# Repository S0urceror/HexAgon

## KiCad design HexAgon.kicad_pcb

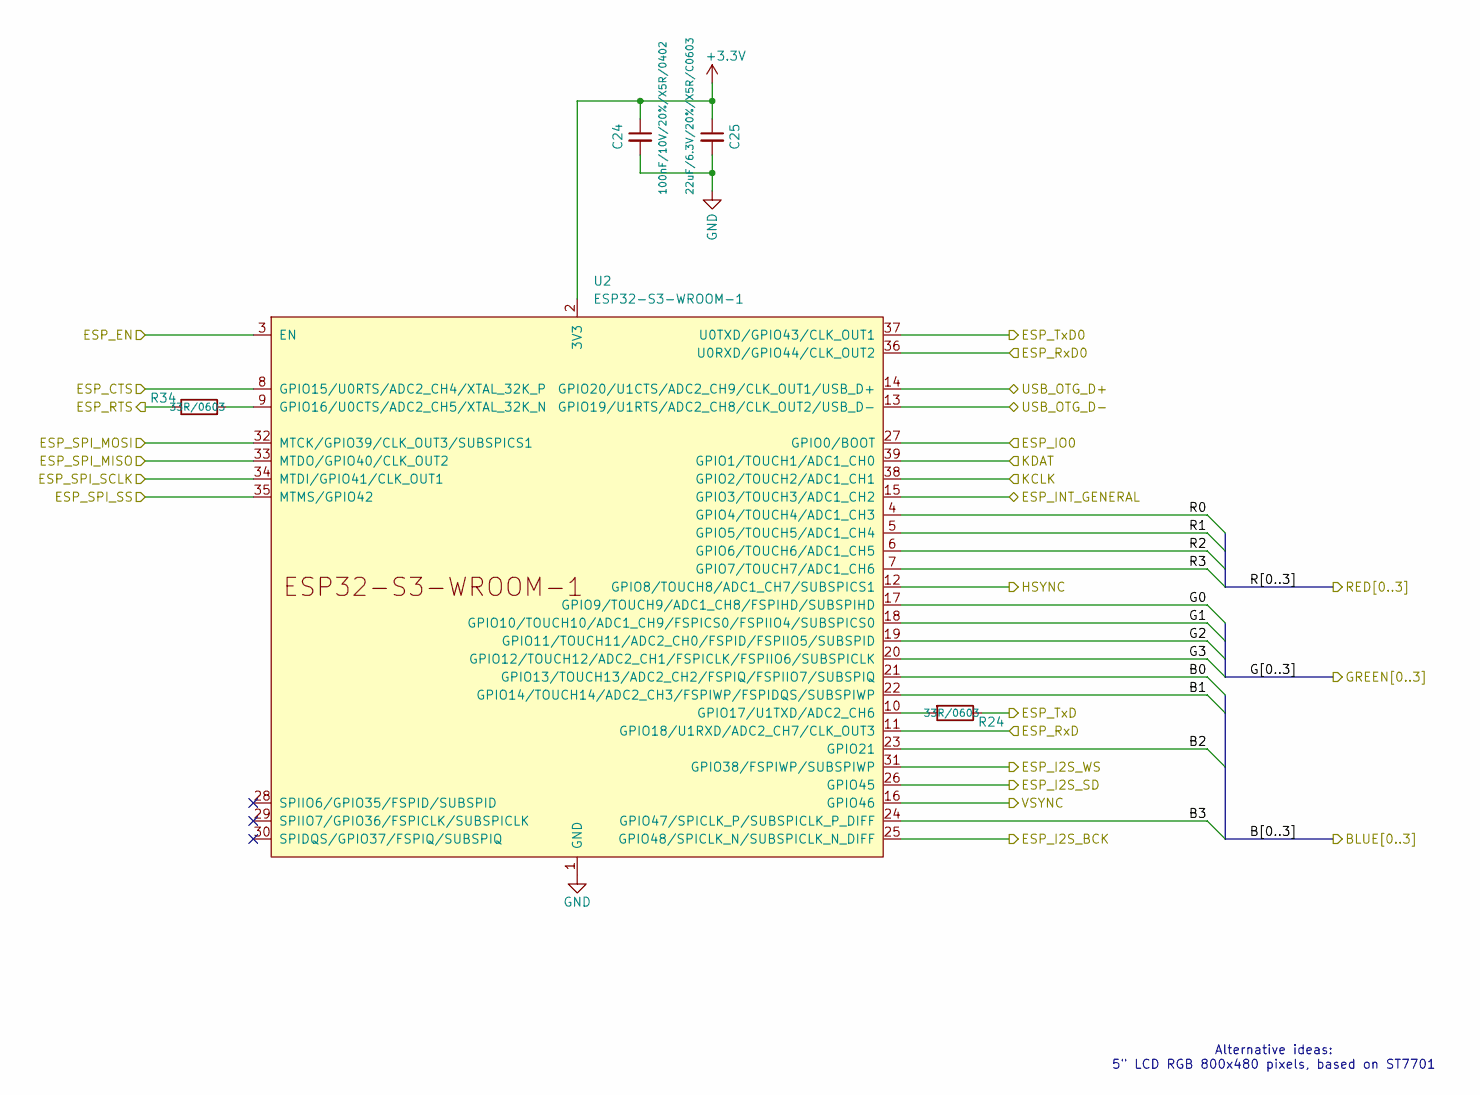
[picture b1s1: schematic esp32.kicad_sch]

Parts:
C24: 100nF/10V/20%/X5R/0402; C_0402_5MIL_DWS
C25: 22uF/6.3V/20%/X5R/C0603; C_0603_5MIL_DWS
R24, R34: 33R/0603; R_0603_5MIL_DWS
U2: ESP32-S3-WROOM-1

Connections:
+3.3V: C24.1, C25.1, U2.2 (3V3); also elsewhere on the board
/Audio/ESP_I2S_BCK: U2.25 (GPIO48/SPICLK_N/SUBSPICLK_N_DIFF); also elsewhere on the board
/Audio/ESP_I2S_SD: U2.26 (GPIO45); also elsewhere on the board
/Audio/ESP_I2S_WS: U2.31 (GPIO38/FSPIWP/SUBSPIWP); also elsewhere on the board
/ESP32 ports/BOOT_MODE: U2.27 (GPIO0/BOOT); also elsewhere on the board
/ESP32 ports/HOST_RXD: U2.37 (U0TXD/GPIO43/CLK_OUT1); also elsewhere on the board
/ESP32 ports/HOST_TXD: U2.36 (U0RXD/GPIO44/CLK_OUT2); also elsewhere on the board
/ESP32 ports/KCLK: U2.38 (GPIO2/TOUCH2/ADC1_CH1); also elsewhere on the board
/ESP32 ports/KDAT: U2.39 (GPIO1/TOUCH1/ADC1_CH0); also elsewhere on the board
/ESP32 ports/USB_OTG_D+: U2.14 (GPIO20/U1CTS/ADC2_CH9/CLK_OUT1/USB_D+); also elsewhere on the board
/ESP32 ports/USB_OTG_D-: U2.13 (GPIO19/U1RTS/ADC2_CH8/CLK_OUT2/USB_D-); also elsewhere on the board
/ESP32/B0: U2.21 (GPIO13/TOUCH13/ADC2_CH2/FSPIQ/FSPIIO7/S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); also elsewhere on the board
/ESP32/B1: U2.22 (GPIO14/TOUCH14/ADC2_CH3/FSPIWP/FSPIDQS/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); also elsewhere on the board
/ESP32/B2: U2.23 (GPIO21); also elsewhere on the board
/ESP32/B3: U2.24 (GPIO47/SPICLK_P/SUBSPICLK_P_DIFF); also elsewhere on the board
/ESP32/ESP_CTS: U2.8 (GPIO15/U0RTS/ADC2_CH4/XTAL_32K_P); also elsewhere on the board
/ESP32/ESP_INT_GENERAL: U2.15 (GPIO3/TOUCH3/ADC1_CH2); also elsewhere on the board
/ESP32/ESP_RTS: R34.1; also elsewhere on the board
/ESP32/ESP_RxD: U2.11 (GPIO18/U1RXD/ADC2_CH7/CLK_OUT3); also elsewhere on the board
/ESP32/ESP_SPI_MISO: U2.33 (MTDO/GPIO40/CLK_OUT2); also elsewhere on the board
/ESP32/ESP_SPI_MOSI: U2.32 (MTCK/GPIO39/CLK_OUT3/SUBSPICS1); also elsewhere on the board
/ESP32/ESP_SPI_SCLK: U2.34 (MTDI/GPIO41/CLK_OUT1); also elsewhere on the board
/ESP32/ESP_SPI_SS: U2.35 (MTMS/GPIO42); also elsewhere on the board
/ESP32/ESP_TxD: R24.1; also elsewhere on the board
/ESP32/G0: U2.17 (GPIO9/TOUCH9/ADC1_CH8/FSPIHD/SUBSPIHD); also elsewhere on the board
/ESP32/G1: U2.18 (GPIO10/TOUCH10/ADC1_CH9/FSPICS0/FSPIIO4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); also elsewhere on the board
/ESP32/G2: U2.19 (GPIO11/TOUCH11/ADC2_CH0/FSPID/FSPIIO5/S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); also elsewhere on the board
/ESP32/G3: U2.20 (GPIO12/TOUCH12/ADC2_CH1/FSPICLK/FSPIIO6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); also elsewhere on the board
/ESP32/HSYNC: U2.12 (GPIO8/TOUCH8/ADC1_CH7/SUBSPICS1); also elsewhere on the board
/ESP32/R0: U2.4 (GPIO4/TOUCH4/ADC1_CH3); also elsewhere on the board
/ESP32/R1: U2.5 (GPIO5/TOUCH5/ADC1_CH4); also elsewhere on the board
/ESP32/R2: U2.6 (GPIO6/TOUCH6/ADC1_CH5); also elsewhere on the board
/ESP32/R3: U2.7 (GPIO7/TOUCH7/ADC1_CH6); also elsewhere on the board
/ESP32/VSYNC: U2.16 (GPIO46); also elsewhere on the board
/EZ80/~RESET: U2.3 (EN); also elsewhere on the board
GND: C24.2, C25.2, U2.1 (GND), U2.40 (GND), U2.41 (GND); also elsewhere on the board
unnamed: R34.2, U2.9 (GPIO16/U0CTS/ADC2_CH5/XTAL_32K_N)
unnamed: R24.2, U2.10 (GPIO17/U1TXD/ADC2_CH6)

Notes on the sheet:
Alternative ideas: 5" LCD RGB 800x480 pixels, based on ST7701

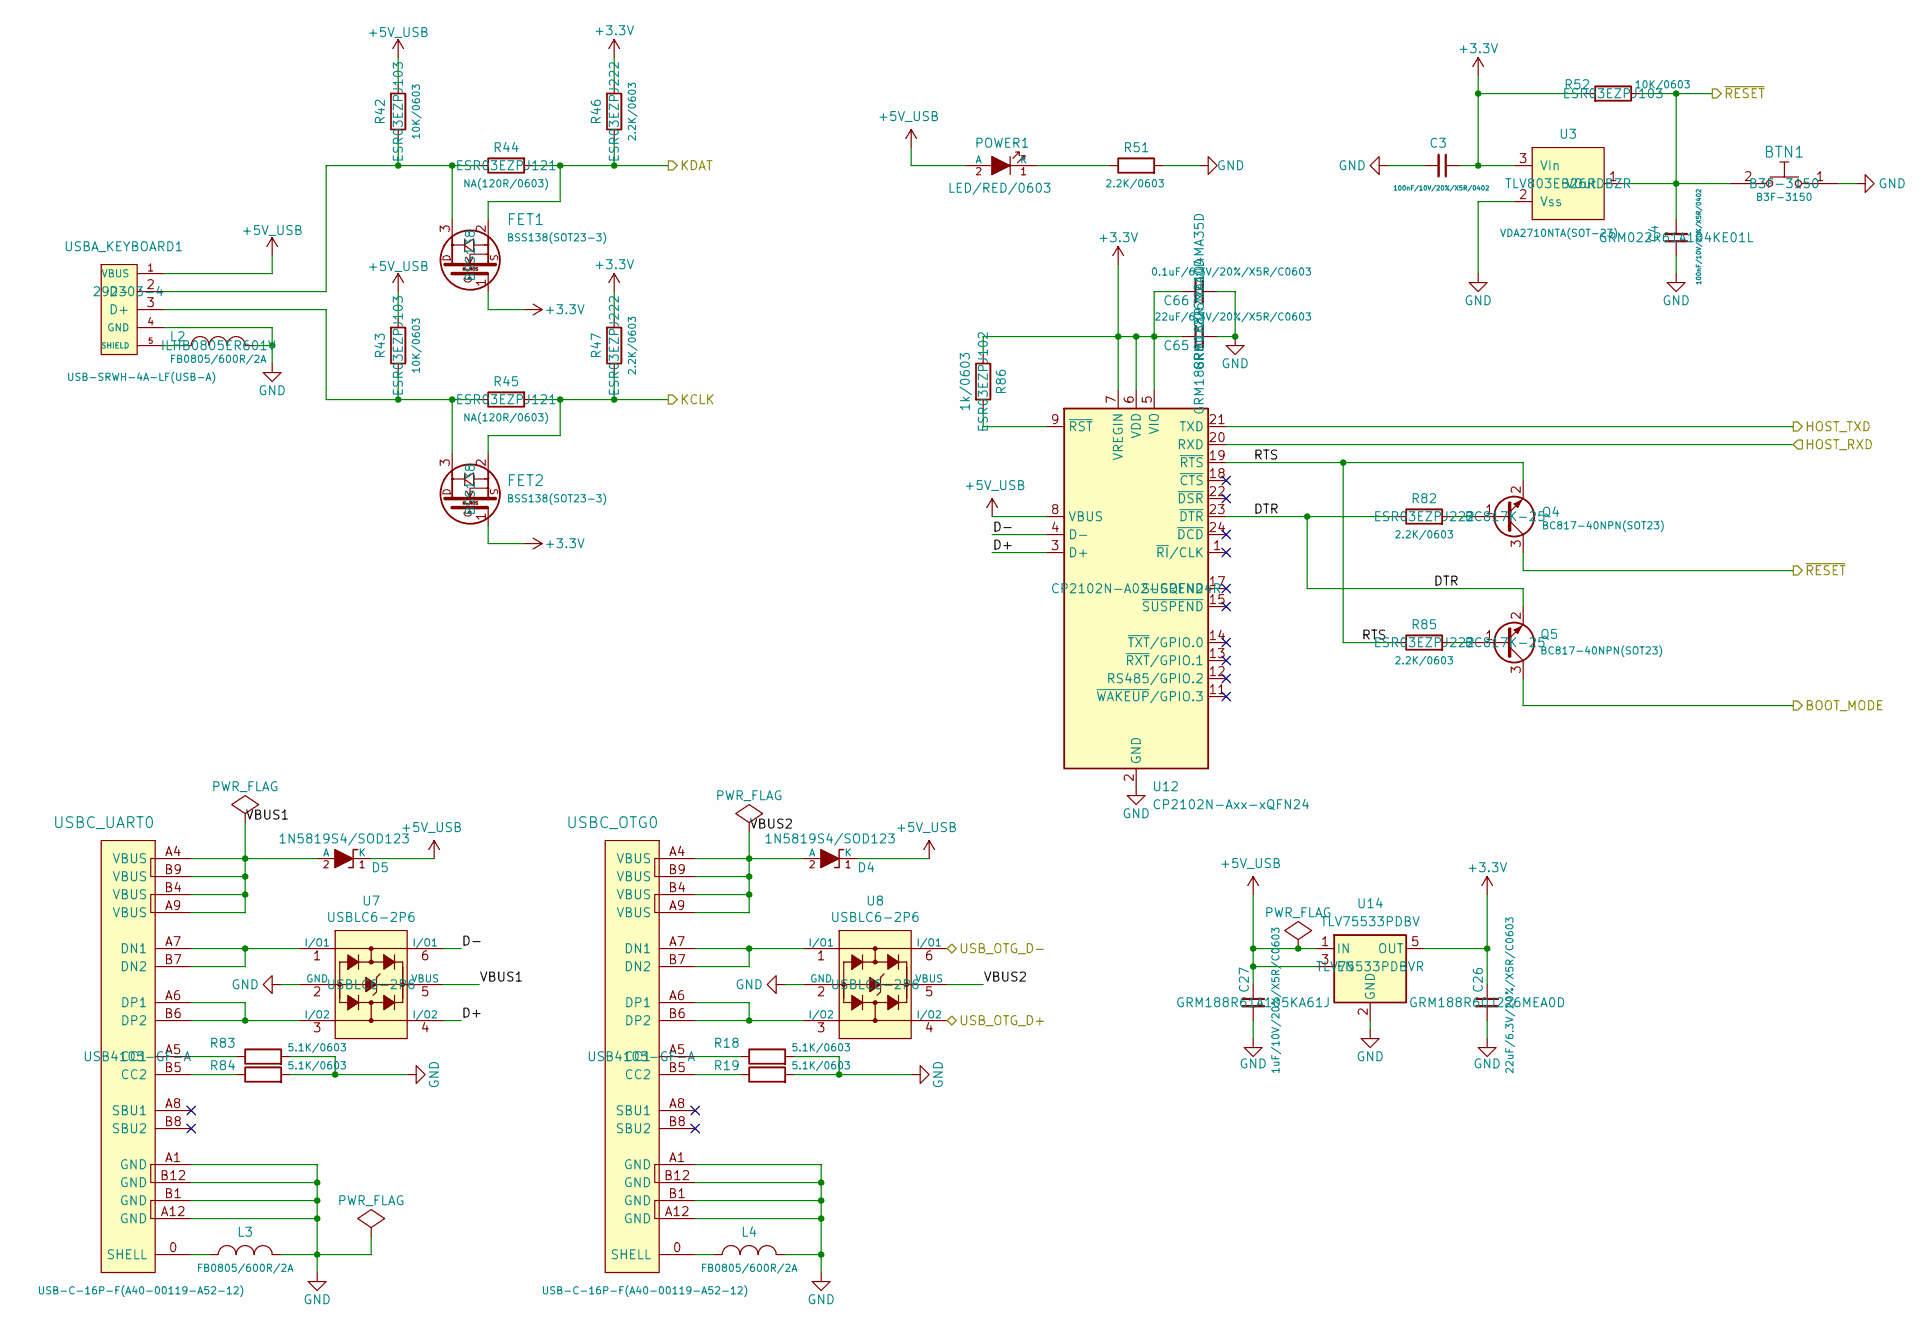
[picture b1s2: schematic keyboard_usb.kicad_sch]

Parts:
BTN1: B3F-3150; B3F-31XX
C3, C4: 100nF/10V/20%/X5R/0402; C_0402_5MIL_DWS
C26, C65: 22uF/6.3V/20%/X5R/C0603; C_0603_5MIL_DWS
C27: 1uF/10V/20%/X5R/C0603; C_0603_5MIL_DWS
C66: 0.1uF/6.3V/20%/X5R/C0603; C_0603_5MIL_DWS
D4, D5: 1N5819S4/SOD123; SOD-123_1C-2A_KA
FET1, FET2: BSS138(SOT23-3); SOT23
L2, L3, L4: FB0805/600R/2A; L_0805_5MIL_DWS
POWER1: LED/RED/0603; LED_0603_KA
Q4, Q5: BC817-40NPN(SOT23); SOT23
R18, R19, R83, R84: 5.1K/0603; R_0603_5MIL_DWS
R42, R43, R52: 10K/0603; R_0603_5MIL_DWS
R44, R45: NA(120R/0603); R_0603_5MIL_DWS
R46, R47, R51, R82, R85: 2.2K/0603; R_0603_5MIL_DWS
R86: 1k/0603; R_0603_5MIL_DWS
U3: VDA2710NTA(SOT-23); SOT-23
U7, U8: USBLC6-2P6; SOT-666
U12: CP2102N-Axx-xQFN24; QFN-24-1EP_4x4mm_P0.5mm_EP2.6x2.6mm
U14: TLV75533PDBV; SOT-23-5
USBA_KEYBOARD1: USB-SRWH-4A-LF(USB-A); USB_PN87520_HOST_PTH
USBC_OTG0: USB-C-16P-F(A40-00119-A52-12); USB2.0_TYPE-C(A40-00119-A52-12)
USBC_UART0: USB-C-16P-F(A40-00119-A52-12); USB2.0_TYPE-C(A40-00119-A52-12)

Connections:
+3.3V: C3.1, C26.1, C65.1, C66.1, FET1.1 (G), FET2.1 (G), R46.2, R47.2, R52.2, R86.1, U3.3 (VIn), U12.5 (VIO), U12.6 (VDD), U12.7 (VREGIN), U14.5 (OUT); also elsewhere on the board
+5V_USB: C27.1, D4.1 (K), D5.1 (K), POWER1.2 (A), R42.2, R43.2, U12.8 (VBUS), U14.1 (IN), U14.3 (EN), USBA_KEYBOARD1.1 (VBUS); also elsewhere on the board
/ESP32 ports/BOOT_MODE: Q5.3 (C); also elsewhere on the board
/ESP32 ports/D+: U7.4 (I/O2), U12.3 (D+)
/ESP32 ports/D-: U7.6 (I/O1), U12.4 (D-)
/ESP32 ports/DTR: Q5.2 (E), R82.1, U12.23 (~DTR)
/ESP32 ports/HOST_RXD: U12.20 (RXD); also elsewhere on the board
/ESP32 ports/HOST_TXD: U12.21 (TXD); also elsewhere on the board
/ESP32 ports/KCLK: FET2.2 (S), R45.2, R47.1; also elsewhere on the board
/ESP32 ports/KDAT: FET1.2 (S), R44.2, R46.1; also elsewhere on the board
/ESP32 ports/RTS: Q4.2 (E), R85.1, U12.19 (~RTS)
/ESP32 ports/USB_OTG_D+: U8.4 (I/O2); also elsewhere on the board
/ESP32 ports/USB_OTG_D-: U8.6 (I/O1); also elsewhere on the board
/ESP32 ports/VBUS1: D5.2 (A), U7.5 (VBUS), USBC_UART0.A4 (VBUS), USBC_UART0.A9 (VBUS), USBC_UART0.B4 (VBUS), USBC_UART0.B9 (VBUS)
/ESP32 ports/VBUS2: D4.2 (A), U8.5 (VBUS), USBC_OTG0.A4 (VBUS), USBC_OTG0.A9 (VBUS), USBC_OTG0.B4 (VBUS), USBC_OTG0.B9 (VBUS)
/EZ80/~RESET: BTN1.2, C4.2, Q4.3 (C), R52.1, U3.1 (VOut); also elsewhere on the board
GND: BTN1.1, C3.2, C4.1, C26.2, C27.2, C65.2, C66.2, L2.2, L3.2, L4.2, R18.2, R19.2, R51.2, R83.2, R84.2, U3.2 (Vss), U7.2 (GND), U8.2 (GND), U12.2 (GND), U12.25 (GND), U14.2 (GND), USBA_KEYBOARD1.4 (GND), USBC_OTG0.A1 (GND), USBC_OTG0.A12 (GND), USBC_OTG0.B1 (GND), USBC_OTG0.B12 (GND), USBC_UART0.A1 (GND), USBC_UART0.A12 (GND), USBC_UART0.B1 (GND), USBC_UART0.B12 (GND); also elsewhere on the board
unnamed: FET1.3 (D), R42.1, R44.1, USBA_KEYBOARD1.2 (D-)
unnamed: FET2.3 (D), R43.1, R45.1, USBA_KEYBOARD1.3 (D+)
unnamed: POWER1.1 (K), R51.1
unnamed: Q4.1 (B), R82.2
unnamed: Q5.1 (B), R85.2
unnamed: R86.2, U12.9 (~RST)
unnamed: L2.1, USBA_KEYBOARD1.5 (SHIELD)
unnamed: R18.1, USBC_OTG0.A5 (CC1)
unnamed: R19.1, USBC_OTG0.B5 (CC2)
unnamed: U8.1 (I/O1), USBC_OTG0.A7 (DN1), USBC_OTG0.B7 (DN2)
unnamed: U8.3 (I/O2), USBC_OTG0.A6 (DP1), USBC_OTG0.B6 (DP2)
unnamed: L4.1, USBC_OTG0.0 (SHELL)
unnamed: R83.1, USBC_UART0.A5 (CC1)
unnamed: R84.1, USBC_UART0.B5 (CC2)
unnamed: U7.1 (I/O1), USBC_UART0.A7 (DN1), USBC_UART0.B7 (DN2)
unnamed: U7.3 (I/O2), USBC_UART0.A6 (DP1), USBC_UART0.B6 (DP2)
unnamed: L3.1, USBC_UART0.0 (SHELL)

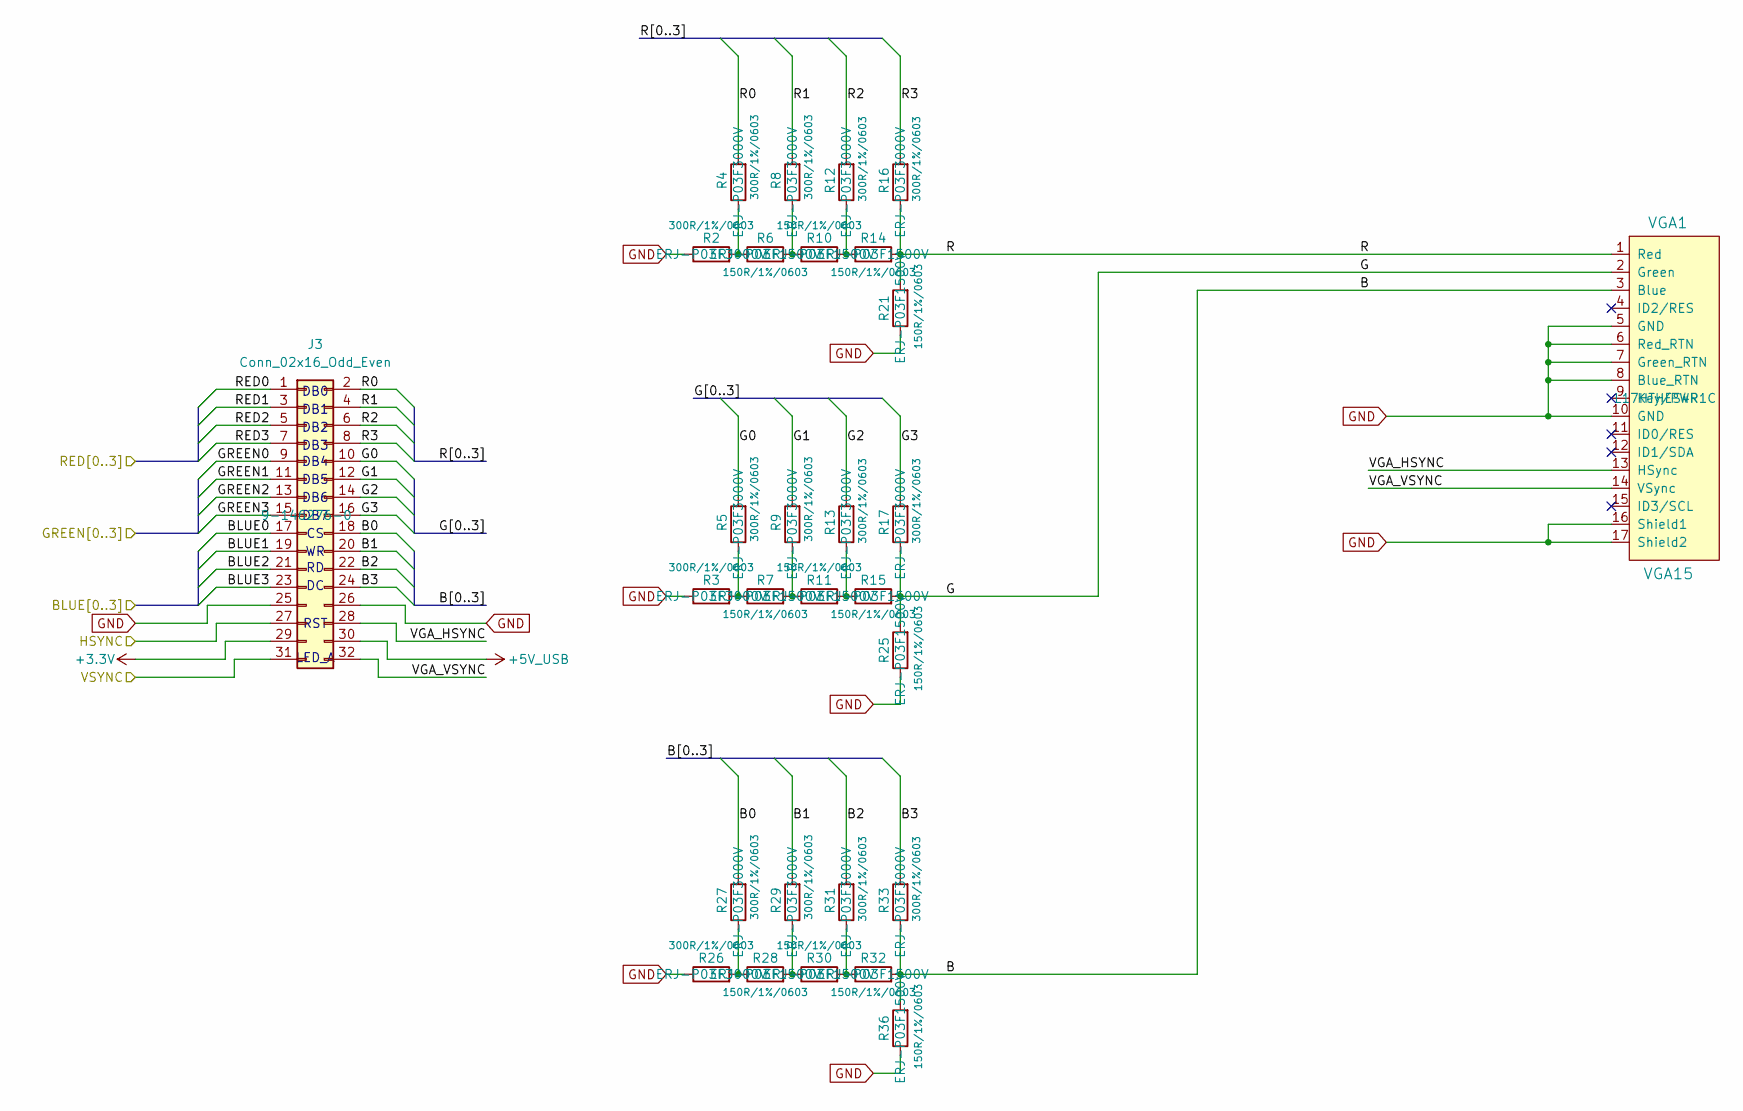
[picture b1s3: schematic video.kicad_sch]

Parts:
J3: Conn_02x16_Odd_Even; PinHeader_2x16_P2.54mm_Vertical_SMD
R2, R3, R4, R5, R8, R9, R12, R13, R16, R17, R26, R27, R29, R31, R33: 300R/1%/0603; R_0603_5MIL_DWS
R6, R7, R10, R11, R14, R15, R21, R25, R28, R30, R32, R36: 150R/1%/0603; R_0603_5MIL_DWS
VGA1: VGA15; VGA15-F(CD0515S21J0)

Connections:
+3.3V: J3.29; also elsewhere on the board
+5V_USB: J3.30; also elsewhere on the board
/ESP32/B0: J3.17; also elsewhere on the board
/ESP32/B1: J3.19; also elsewhere on the board
/ESP32/B2: J3.21; also elsewhere on the board
/ESP32/B3: J3.23; also elsewhere on the board
/ESP32/G0: J3.9; also elsewhere on the board
/ESP32/G1: J3.11; also elsewhere on the board
/ESP32/G2: J3.13; also elsewhere on the board
/ESP32/G3: J3.15; also elsewhere on the board
/ESP32/HSYNC: J3.27; also elsewhere on the board
/ESP32/R0: J3.1; also elsewhere on the board
/ESP32/R1: J3.3; also elsewhere on the board
/ESP32/R2: J3.5; also elsewhere on the board
/ESP32/R3: J3.7; also elsewhere on the board
/ESP32/VSYNC: J3.31; also elsewhere on the board
/Video/B: R32.2, R33.1, R36.2, VGA1.3 (Blue)
/Video/B0: J3.18, R27.2
/Video/B1: J3.20, R29.2
/Video/B2: J3.22, R31.2
/Video/B3: J3.24, R33.2
/Video/G: R15.2, R17.1, R25.2, VGA1.2 (Green)
/Video/G0: J3.10, R5.2
/Video/G1: J3.12, R9.2
/Video/G2: J3.14, R13.2
/Video/G3: J3.16, R17.2
/Video/R: R14.2, R16.1, R21.2, VGA1.1 (Red)
/Video/R0: J3.2, R4.2
/Video/R1: J3.4, R8.2
/Video/R2: J3.6, R12.2
/Video/R3: J3.8, R16.2
/Video/VGA_HSYNC: J3.28, VGA1.13 (HSync)
/Video/VGA_VSYNC: J3.32, VGA1.14 (VSync)
GND: J3.25, J3.26, R2.1, R3.1, R21.1, R25.1, R26.1, R36.1, VGA1.5 (GND), VGA1.6 (Red_RTN), VGA1.7 (Green_RTN), VGA1.8 (Blue_RTN), VGA1.10 (GND), VGA1.16 (Shield1), VGA1.17 (Shield2); also elsewhere on the board
unnamed: R2.2, R4.1, R6.1
unnamed: R3.2, R5.1, R7.1
unnamed: R6.2, R8.1, R10.1
unnamed: R10.2, R12.1, R14.1
unnamed: R7.2, R9.1, R11.1
unnamed: R11.2, R13.1, R15.1
unnamed: R26.2, R27.1, R28.1
unnamed: R28.2, R29.1, R30.1
unnamed: R30.2, R31.1, R32.1

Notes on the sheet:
DB3
DB4
LED_A
DB1
DB6
DB2
DB7
RST
DB5
DB0

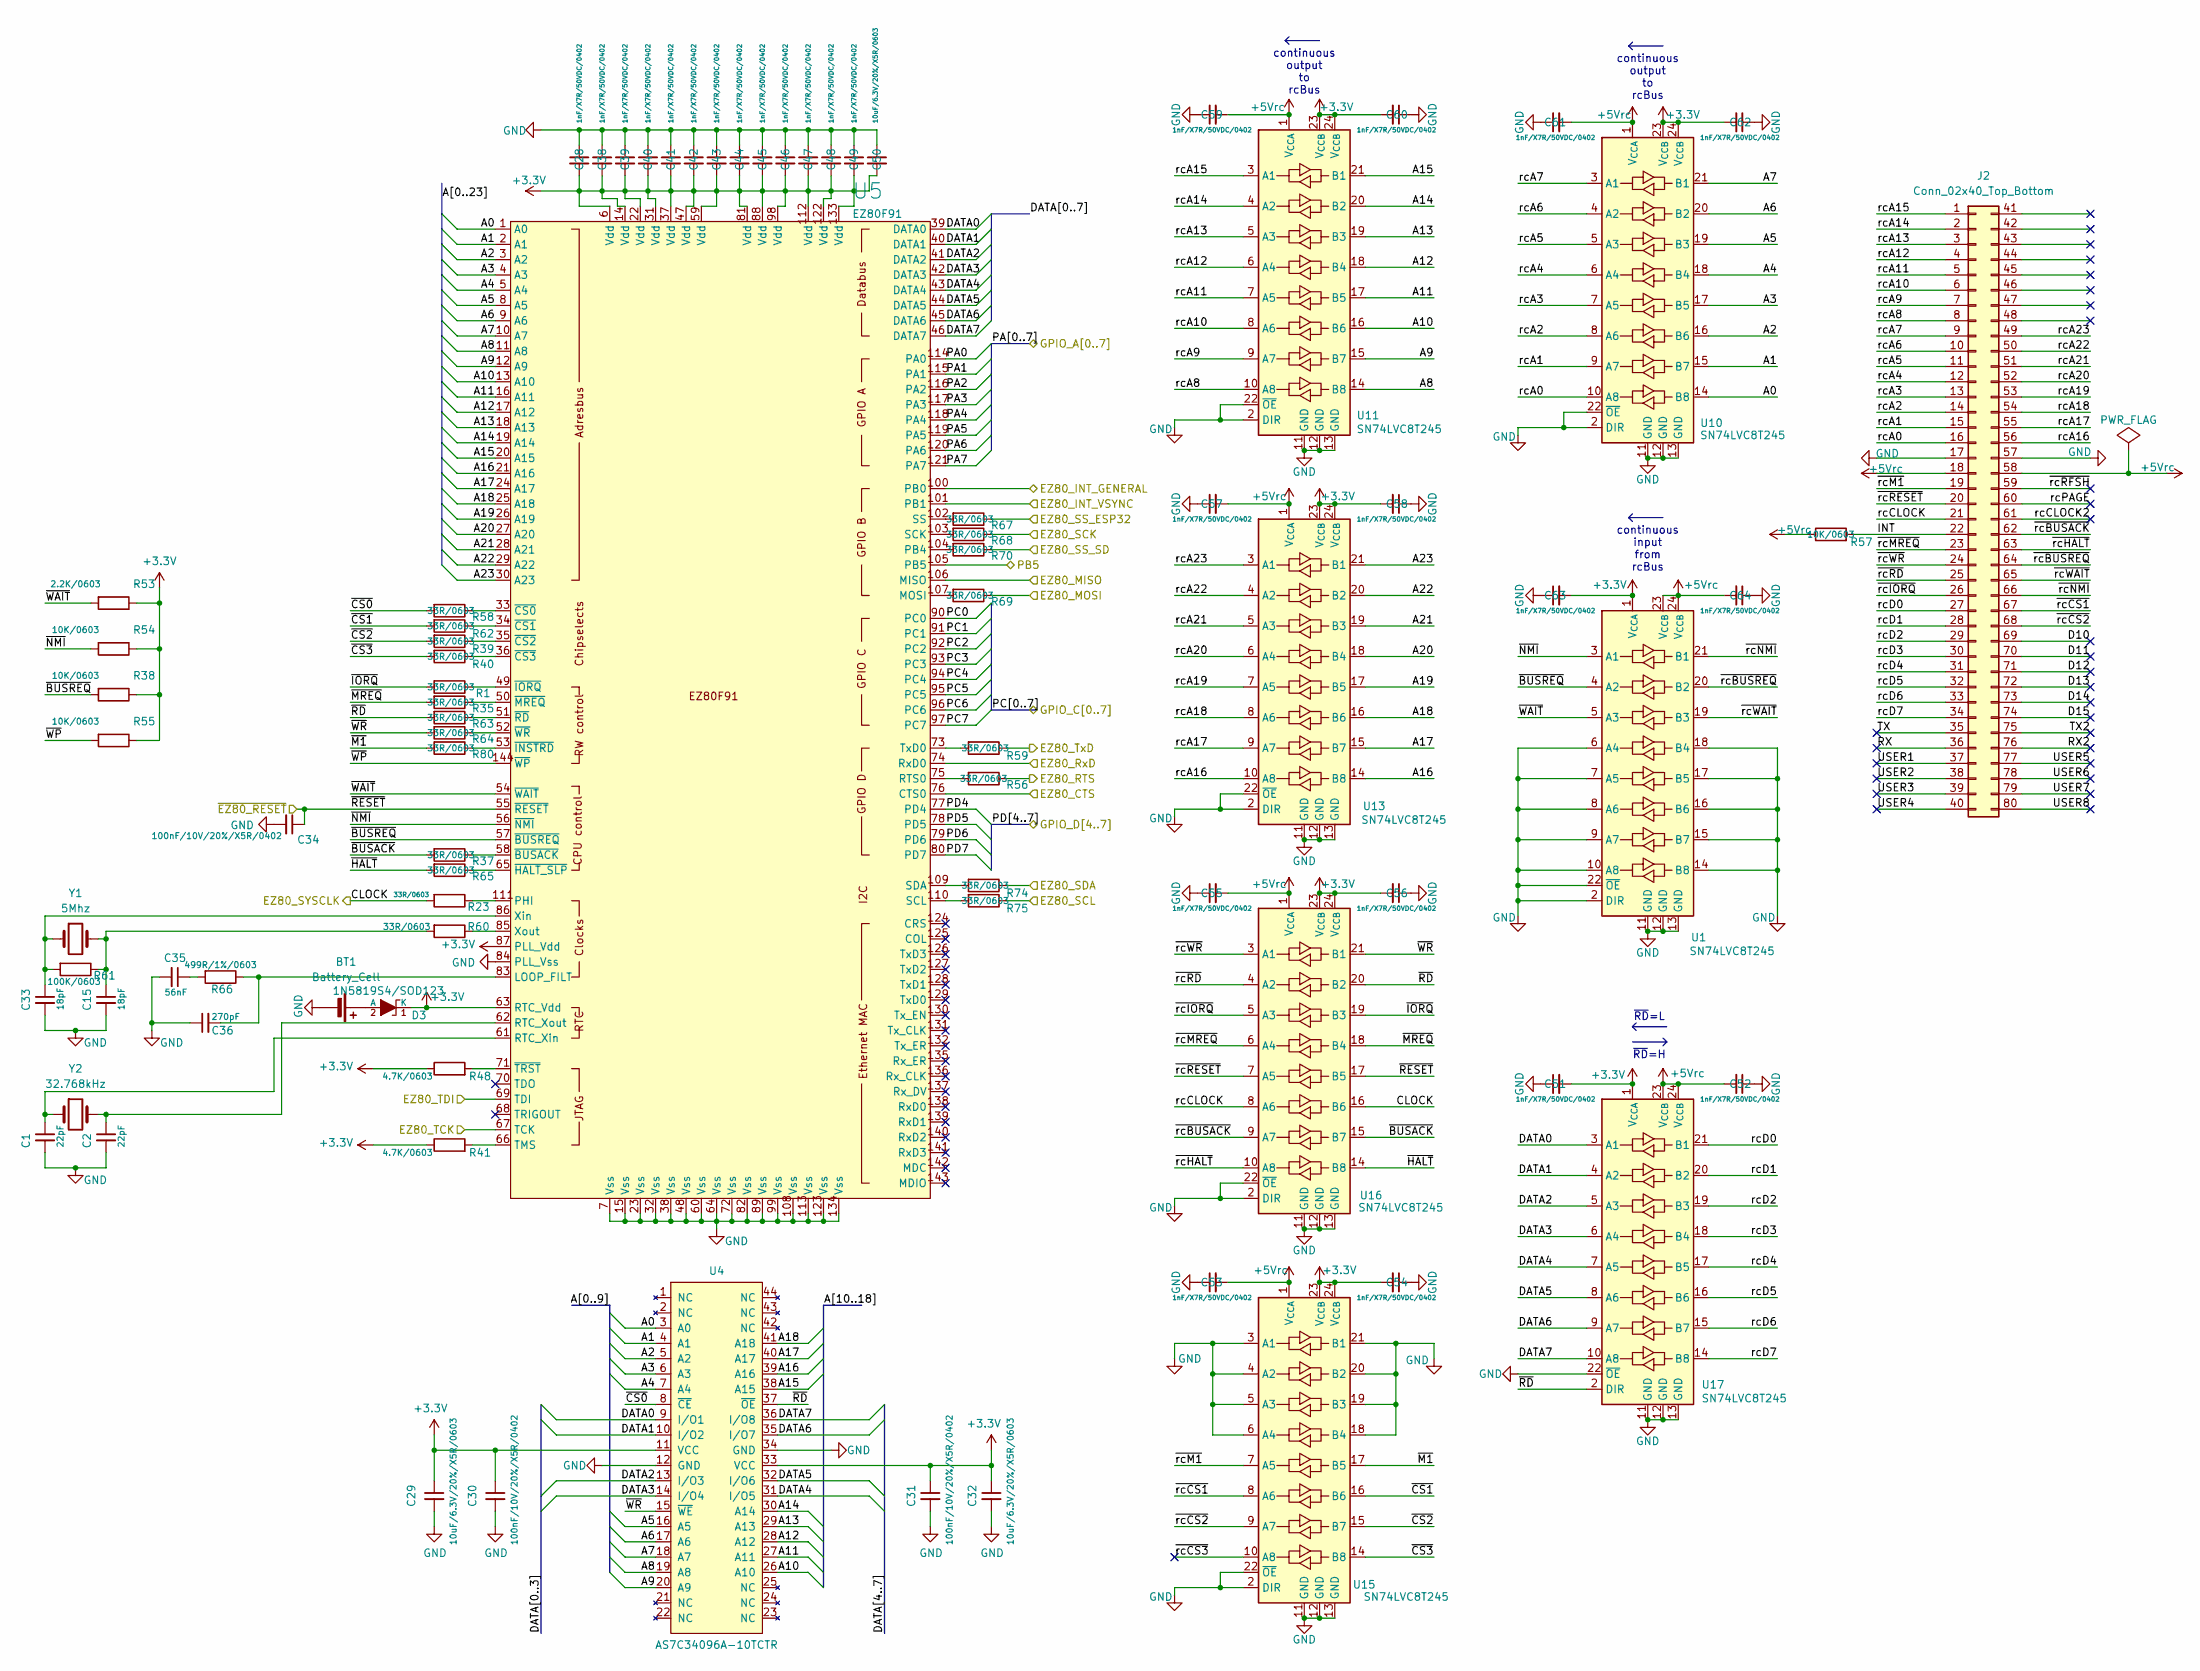
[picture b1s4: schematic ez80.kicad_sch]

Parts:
BT1: Battery_Cell; PinHeader_1x02_P2.54mm_Vertical
C1, C2: 22pF; C_0402_5MIL_DWS
C15, C33: 18pF; C_0402_5MIL_DWS
C28, C38, C39, C40, C41, C42, C43, C44, C45, C46, C47, C48, C49, C51, C52, C53, C54, C55, C56, C57, C58, C59, C60, C61, C62, C63, C64: 1nF/X7R/50VDC/0402; C_0402_5MIL_DWS
C29, C32, C50: 10uF/6.3V/20%/X5R/0603; C_0603_5MIL_DWS
C30, C31, C34: 100nF/10V/20%/X5R/0402; C_0402_5MIL_DWS
C35: 56nF; C_0402_5MIL_DWS
C36: 270pF; C_0402_5MIL_DWS
D3: 1N5819S4/SOD123; SOD-123_1C-2A_KA
J2: Conn_02x40_Top_Bottom; PinHeader_2x40_P2.54mm_Vertical
R1, R23, R35, R37, R39, R40, R56, R58, R59, R60, R62, R63, R64, R65, R67, R68, R69, R70, R74, R75, R80: 33R/0603; R_0603_5MIL_DWS
R38, R54, R55, R57: 10K/0603; R_0603_5MIL_DWS
R41, R48: 4.7K/0603; R_0603_5MIL_DWS
R53: 2.2K/0603; R_0603_5MIL_DWS
R61: 100K/0603; R_0603_5MIL_DWS
R66: 499R/1%/0603; R_0603_5MIL_DWS
U1, U10, U11, U13, U15, U16, U17: SN74LVC8T245; TSSOP-24_4.4x7.8mm_P0.65mm
U4: AS7C34096A-10TCTR; TSOP-44_Pitch-0.80mm_18.80x11.80x1.20mm
U5: EZ80F91; LQFP-144-1EP_20x20mm_P0.5mm_EP6.5x6.5mm
Y1: 5Mhz; Crystal_SMD_HC49-SD
Y2: 32.768kHz; Crystal_C26-LF_D2.1mm_L6.5mm_Horizontal

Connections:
+3.3V: C28.2, C29.1, C30.1, C31.1, C32.1, C38.2, C39.2, C40.2, C41.2, C42.2, C43.2, C44.2, C45.2, C46.2, C47.2, C48.2, C49.2, C50.2, C51.2, C54.2, C56.2, C58.2, C60.2, C62.2, C63.2, D3.1 (K), R38.1, R41.1, R48.1, R53.1, R54.1, R55.1, U1.1 (V_{CCA}), U4.11 (VCC), U4.33 (VCC), U5.6 (Vdd), U5.14 (Vdd), U5.22 (Vdd), U5.31 (Vdd), U5.37 (Vdd), U5.47 (Vdd), U5.59 (Vdd), U5.63 (RTC_Vdd), U5.81 (Vdd), U5.87 (PLL_Vdd), U5.88 (Vdd), U5.98 (Vdd), U5.112 (Vdd), U5.122 (Vdd), U5.133 (Vdd), U10.23 (V_{CCB}), U10.24 (V_{CCB}), U11.23 (V_{CCB}), U11.24 (V_{CCB}), U13.23 (V_{CCB}), U13.24 (V_{CCB}), U15.23 (V_{CCB}), U15.24 (V_{CCB}), U16.23 (V_{CCB}), U16.24 (V_{CCB}), U17.1 (V_{CCA}); also elsewhere on the board
+5Vrc: C52.2, C53.2, C55.2, C57.2, C59.2, C61.2, C64.2, J2.18, J2.58, R57.1, U1.23 (V_{CCB}), U1.24 (V_{CCB}), U10.1 (V_{CCA}), U11.1 (V_{CCA}), U13.1 (V_{CCA}), U15.1 (V_{CCA}), U16.1 (V_{CCA}), U17.23 (V_{CCB}), U17.24 (V_{CCB})
/ESP32/ESP_CTS: R56.1; also elsewhere on the board
/ESP32/ESP_INT_GENERAL: U5.100 (PB0); also elsewhere on the board
/ESP32/ESP_RTS: U5.76 (CTS0); also elsewhere on the board
/ESP32/ESP_RxD: R59.1; also elsewhere on the board
/ESP32/ESP_SPI_MISO: U5.106 (MISO); also elsewhere on the board
/ESP32/ESP_SPI_MOSI: R69.1; also elsewhere on the board
/ESP32/ESP_SPI_SCLK: R68.1; also elsewhere on the board
/ESP32/ESP_SPI_SS: R67.1; also elsewhere on the board
/ESP32/ESP_TxD: U5.74 (RxD0); also elsewhere on the board
/ESP32/VSYNC: U5.101 (PB1); also elsewhere on the board
/EZ80 ports/EZ80_SCL: R75.1; also elsewhere on the board
/EZ80 ports/EZ80_SDA: R74.1; also elsewhere on the board
/EZ80 ports/EZ80_SS_SD: R70.1; also elsewhere on the board
/EZ80 ports/EZ80_TCK: U5.67 (TCK); also elsewhere on the board
/EZ80 ports/EZ80_TDI: U5.69 (TDI); also elsewhere on the board
/EZ80 ports/GPIO_B5: U5.105 (PB5); also elsewhere on the board
/EZ80/A0: U4.3 (A0), U5.1 (A0), U10.14 (B8)
/EZ80/A1: U4.4 (A1), U5.2 (A1), U10.15 (B7)
/EZ80/A2: U4.5 (A2), U5.3 (A2), U10.16 (B6)
/EZ80/A3: U4.6 (A3), U5.4 (A3), U10.17 (B5)
/EZ80/A4: U4.7 (A4), U5.5 (A4), U10.18 (B4)
/EZ80/A5: U4.16 (A5), U5.8 (A5), U10.19 (B3)
/EZ80/A6: U4.17 (A6), U5.9 (A6), U10.20 (B2)
/EZ80/A7: U4.18 (A7), U5.10 (A7), U10.21 (B1)
/EZ80/A8: U4.19 (A8), U5.11 (A8), U11.14 (B8)
/EZ80/A9: U4.20 (A9), U5.12 (A9), U11.15 (B7)
/EZ80/A10: U4.26 (A10), U5.13 (A10), U11.16 (B6)
/EZ80/A11: U4.27 (A11), U5.16 (A11), U11.17 (B5)
/EZ80/A12: U4.28 (A12), U5.17 (A12), U11.18 (B4)
/EZ80/A13: U4.29 (A13), U5.18 (A13), U11.19 (B3)
/EZ80/A14: U4.30 (A14), U5.19 (A14), U11.20 (B2)
/EZ80/A15: U4.38 (A15), U5.20 (A15), U11.21 (B1)
/EZ80/A16: U4.39 (A16), U5.21 (A16), U13.14 (B8)
/EZ80/A17: U4.40 (A17), U5.24 (A17), U13.15 (B7)
/EZ80/A18: U4.41 (A18), U5.25 (A18), U13.16 (B6)
/EZ80/A19: U5.26 (A19), U13.17 (B5)
/EZ80/A20: U5.27 (A20), U13.18 (B4)
/EZ80/A21: U5.28 (A21), U13.19 (B3)
/EZ80/A22: U5.29 (A22), U13.20 (B2)
/EZ80/A23: U5.30 (A23), U13.21 (B1)
/EZ80/CLOCK: R23.2, U16.16 (B6); also elsewhere on the board
/EZ80/D10: J2.69
/EZ80/D11: J2.70
/EZ80/D12: J2.71
/EZ80/D13: J2.72
/EZ80/D14: J2.73
/EZ80/D15: J2.74
/EZ80/DATA0: U4.9 (I/O1), U5.39 (DATA0), U17.3 (A1)
/EZ80/DATA1: U4.10 (I/O2), U5.40 (DATA1), U17.4 (A2)
/EZ80/DATA2: U4.13 (I/O3), U5.41 (DATA2), U17.5 (A3)
/EZ80/DATA3: U4.14 (I/O4), U5.42 (DATA3), U17.6 (A4)
/EZ80/DATA4: U4.31 (I/O5), U5.43 (DATA4), U17.7 (A5)
/EZ80/DATA5: U4.32 (I/O6), U5.44 (DATA5), U17.8 (A6)
/EZ80/DATA6: U4.35 (I/O7), U5.45 (DATA6), U17.9 (A7)
/EZ80/DATA7: U4.36 (I/O8), U5.46 (DATA7), U17.10 (A8)
/EZ80/INT: J2.22, R57.2
/EZ80/PA0: U5.114 (PA0); also elsewhere on the board
/EZ80/PA1: U5.115 (PA1); also elsewhere on the board
/EZ80/PA2: U5.116 (PA2); also elsewhere on the board
/EZ80/PA3: U5.117 (PA3); also elsewhere on the board
/EZ80/PA4: U5.118 (PA4); also elsewhere on the board
/EZ80/PA5: U5.119 (PA5); also elsewhere on the board
/EZ80/PA6: U5.120 (PA6); also elsewhere on the board
/EZ80/PA7: U5.121 (PA7); also elsewhere on the board
/EZ80/PC0: U5.90 (PC0); also elsewhere on the board
/EZ80/PC1: U5.91 (PC1); also elsewhere on the board
/EZ80/PC2: U5.92 (PC2); also elsewhere on the board
/EZ80/PC3: U5.93 (PC3); also elsewhere on the board
/EZ80/PC4: U5.94 (PC4); also elsewhere on the board
/EZ80/PC5: U5.95 (PC5); also elsewhere on the board
/EZ80/PC6: U5.96 (PC6); also elsewhere on the board
/EZ80/PC7: U5.97 (PC7); also elsewhere on the board
/EZ80/PD4: U5.77 (PD4); also elsewhere on the board
/EZ80/PD5: U5.78 (PD5); also elsewhere on the board
/EZ80/PD6: U5.79 (PD6); also elsewhere on the board
/EZ80/PD7: U5.80 (PD7); also elsewhere on the board
/EZ80/RX: J2.36
/EZ80/RX2: J2.76
/EZ80/TX: J2.35
/EZ80/TX2: J2.75
/EZ80/USER1: J2.37
/EZ80/USER2: J2.38
/EZ80/USER3: J2.39
/EZ80/USER4: J2.40
/EZ80/USER5: J2.77
/EZ80/USER6: J2.78
/EZ80/USER7: J2.79
/EZ80/USER8: J2.80
/EZ80/rcA0: J2.16, U10.10 (A8)
/EZ80/rcA1: J2.15, U10.9 (A7)
/EZ80/rcA2: J2.14, U10.8 (A6)
/EZ80/rcA3: J2.13, U10.7 (A5)
/EZ80/rcA4: J2.12, U10.6 (A4)
/EZ80/rcA5: J2.11, U10.5 (A3)
/EZ80/rcA6: J2.10, U10.4 (A2)
/EZ80/rcA7: J2.9, U10.3 (A1)
/EZ80/rcA8: J2.8, U11.10 (A8)
/EZ80/rcA9: J2.7, U11.9 (A7)
/EZ80/rcA10: J2.6, U11.8 (A6)
/EZ80/rcA11: J2.5, U11.7 (A5)
/EZ80/rcA12: J2.4, U11.6 (A4)
/EZ80/rcA13: J2.3, U11.5 (A3)
/EZ80/rcA14: J2.2, U11.4 (A2)
/EZ80/rcA15: J2.1, U11.3 (A1)
/EZ80/rcA16: J2.56, U13.10 (A8)
/EZ80/rcA17: J2.55, U13.9 (A7)
/EZ80/rcA18: J2.54, U13.8 (A6)
/EZ80/rcA19: J2.53, U13.7 (A5)
/EZ80/rcA20: J2.52, U13.6 (A4)
/EZ80/rcA21: J2.51, U13.5 (A3)
/EZ80/rcA22: J2.50, U13.4 (A2)
/EZ80/rcA23: J2.49, U13.3 (A1)
/EZ80/rcCLOCK: J2.21, U16.8 (A6)
/EZ80/rcCLOCK2: J2.61
/EZ80/rcD0: J2.27, U17.21 (B1)
/EZ80/rcD1: J2.28, U17.20 (B2)
/EZ80/rcD2: J2.29, U17.19 (B3)
/EZ80/rcD3: J2.30, U17.18 (B4)
/EZ80/rcD4: J2.31, U17.17 (B5)
/EZ80/rcD5: J2.32, U17.16 (B6)
/EZ80/rcD6: J2.33, U17.15 (B7)
/EZ80/rcD7: J2.34, U17.14 (B8)
/EZ80/rcPAGE: J2.60
/EZ80/~BUSACK: R37.2, U16.15 (B7)
/EZ80/~BUSREQ: R38.2, U1.4 (A2), U5.57 (~BUSREQ)
/EZ80/~CS0: R58.2, U4.8 (~CE)
/EZ80/~CS1: R62.2, U15.16 (B6)
/EZ80/~CS2: R39.2, U15.15 (B7)
/EZ80/~CS3: R40.2, U15.14 (B8)
/EZ80/~HALT: R65.2, U16.14 (B8)
/EZ80/~IORQ: R1.2, U16.19 (B3)
/EZ80/~M1: R80.2, U15.17 (B5)
/EZ80/~MREQ: R35.2, U16.18 (B4)
/EZ80/~NMI: R54.2, U1.3 (A1), U5.56 (~NMI)
/EZ80/~RD: R63.2, U4.37 (~OE), U16.20 (B2), U17.2 (DIR)
/EZ80/~RESET: C34.1, U5.55 (~RESET), U16.17 (B5); also elsewhere on the board
/EZ80/~WAIT: R53.2, U1.5 (A3), U5.54 (~WAIT)
/EZ80/~WP: R55.2, U5.144 (~WP)
/EZ80/~WR: R64.2, U4.15 (~WE), U16.21 (B1)
/EZ80/~rcBUSACK: J2.62, U16.9 (A7)
/EZ80/~rcBUSREQ: J2.64, U1.20 (B2)
/EZ80/~rcCS1: J2.67, U15.8 (A6)
/EZ80/~rcCS2: J2.68, U15.9 (A7)
/EZ80/~rcCS3: U15.10 (A8)
/EZ80/~rcHALT: J2.63, U16.10 (A8)
/EZ80/~rcIORQ: J2.26, U16.5 (A3)
/EZ80/~rcM1: J2.19, U15.7 (A5)
/EZ80/~rcMREQ: J2.23, U16.6 (A4)
/EZ80/~rcNMI: J2.66, U1.21 (B1)
/EZ80/~rcRD: J2.25, U16.4 (A2)
/EZ80/~rcRESET: J2.20, U16.7 (A5)
/EZ80/~rcRFSH: J2.59
/EZ80/~rcWAIT: J2.65, U1.19 (B3)
/EZ80/~rcWR: J2.24, U16.3 (A1)
GND: BT1.2 (-), C1.2, C2.2, C15.2, C28.1, C29.2, C30.2, C31.2, C32.2, C33.2, C34.2, C35.2, C36.1, C38.1, C39.1, C40.1, C41.1, C42.1, C43.1, C44.1, C45.1, C46.1, C47.1, C48.1, C49.1, C50.1, C51.1, C52.1, C53.1, C54.1, C55.1, C56.1, C57.1, C58.1, C59.1, C60.1, C61.1, C62.1, C63.1, C64.1, J2.17, J2.57, U1.2 (DIR), U1.6 (A4), U1.7 (A5), U1.8 (A6), U1.9 (A7), U1.10 (A8), U1.11 (GND), U1.12 (GND), U1.13 (GND), U1.14 (B8), U1.15 (B7), U1.16 (B6), U1.17 (B5), U1.18 (B4), U1.22 (~OE), U4.12 (GND), U4.34 (GND), U5.7 (Vss), U5.15 (Vss), U5.23 (Vss), U5.32 (Vss), U5.38 (Vss), U5.48 (Vss), U5.60 (Vss), U5.64 (Vss), U5.72 (Vss), U5.82 (Vss), U5.84 (PLL_Vss), U5.89 (Vss), U5.99 (Vss), U5.108 (Vss), U5.113 (Vss), U5.123 (Vss), U5.134 (Vss), U10.2 (DIR), U10.11 (GND), U10.12 (GND), U10.13 (GND), U10.22 (~OE), U11.2 (DIR), U11.11 (GND), U11.12 (GND), U11.13 (GND), U11.22 (~OE), U13.2 (DIR), U13.11 (GND), U13.12 (GND), U13.13 (GND), U13.22 (~OE), U15.2 (DIR), U15.3 (A1), U15.4 (A2), U15.5 (A3), U15.6 (A4), U15.11 (GND), U15.12 (GND), U15.13 (GND), U15.18 (B4), U15.19 (B3), U15.20 (B2), U15.21 (B1), U15.22 (~OE), U16.2 (DIR), U16.11 (GND), U16.12 (GND), U16.13 (GND), U16.22 (~OE), U17.11 (GND), U17.12 (GND), U17.13 (GND), U17.22 (~OE); also elsewhere on the board
unnamed: BT1.1 (+), D3.2 (A)
unnamed: C15.1, R60.2, R61.1, Y1.2
unnamed: C35.1, R66.2
unnamed: R59.2, U5.73 (TxD0)
unnamed: C36.2, R66.1, U5.83 (LOOP_FILT)
unnamed: R67.2, U5.102 (SS)
unnamed: R68.2, U5.103 (SCK)
unnamed: R70.2, U5.104 (PB4)
unnamed: R69.2, U5.107 (MOSI)
unnamed: R56.2, U5.75 (RTS0)
unnamed: R23.1, U5.111 (PHI)
unnamed: C1.1, U5.61 (RTC_Xin), Y2.1
unnamed: C2.1, U5.62 (RTC_Xout), Y2.2
unnamed: R75.2, U5.110 (SCL)
unnamed: R74.2, U5.109 (SDA)
unnamed: R41.2, U5.66 (TMS)
unnamed: C33.1, R61.2, U5.86 (Xin), Y1.1
unnamed: R60.1, U5.85 (Xout)
unnamed: R37.1, U5.58 (~BUSACK)
unnamed: R58.1, U5.33 (~CS0)
unnamed: R62.1, U5.34 (~CS1)
unnamed: R39.1, U5.35 (~CS2)
unnamed: R40.1, U5.36 (~CS3)
unnamed: R65.1, U5.65 (~HALT_SLP)
unnamed: R80.1, U5.53 (~INSTRD)
unnamed: R1.1, U5.49 (~IORQ)
unnamed: R35.1, U5.50 (~MREQ)
unnamed: R63.1, U5.51 (~RD)
unnamed: R48.2, U5.71 (~TRST)
unnamed: R64.1, U5.52 (~WR)

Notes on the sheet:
continuous output to rcBus
~{RD}=L
continuous input from rcBus
~{RD}=H

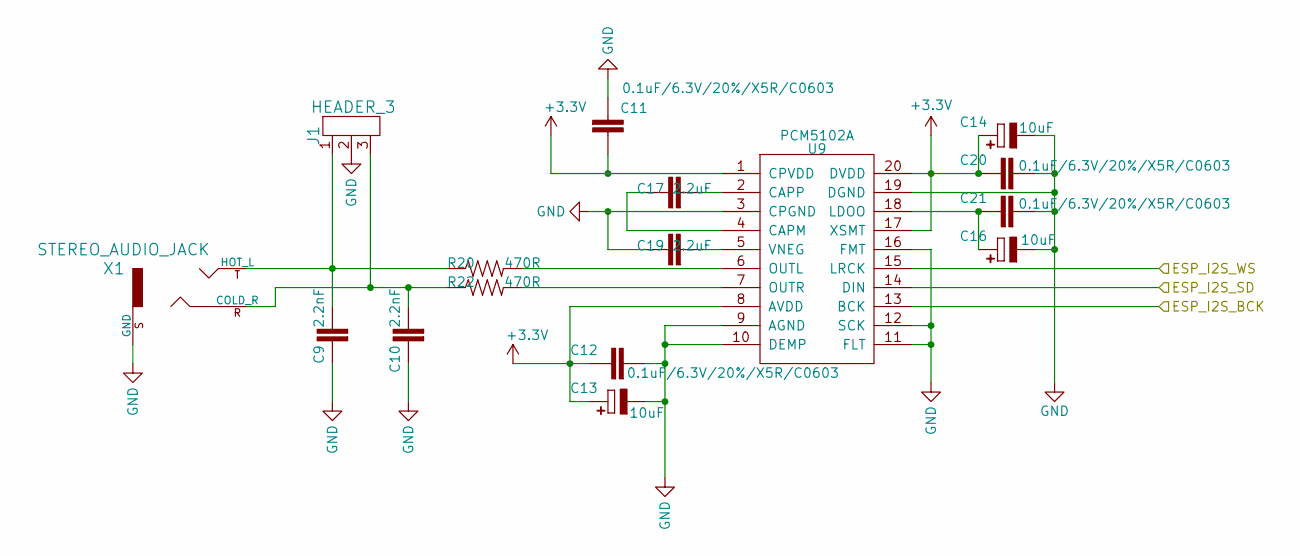
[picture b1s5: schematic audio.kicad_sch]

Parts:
C9, C10: 2.2nF; C_0603_5MIL_DWS
C11, C12, C20, C21: 0.1uF/6.3V/20%/X5R/C0603; C_0603_5MIL_DWS
C13, C14, C16: 10uF; C_0603_5MIL_DWS
C17, C19: 2.2uF; C_0603_5MIL_DWS
J1: HEADER_3; PinHeader_1x03_P2.54mm_Vertical
R20, R22: 470R; R_0603_5MIL_DWS
U9: PCM5102A; TSSOP-20_4.4x6.5mm_P0.65mm
X1: STEREO_AUDIO_JACK; Jack_3.5mm_CUI_SJ-3523-SMT_Horizontal

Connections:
+3.3V: C11.2, C12.1, C13.1 (+), C14.1 (+), C20.1, U9.1 (CPVDD), U9.8 (AVDD), U9.17 (XSMT), U9.20 (DVDD); also elsewhere on the board
/Audio/ESP_I2S_BCK: U9.13 (BCK); also elsewhere on the board
/Audio/ESP_I2S_SD: U9.14 (DIN); also elsewhere on the board
/Audio/ESP_I2S_WS: U9.15 (LRCK); also elsewhere on the board
GND: C9.1, C10.1, C11.1, C12.2, C13.2 (-), C14.2 (-), C16.2 (-), C19.1, C20.2, C21.2, J1.2, U9.3 (CPGND), U9.9 (AGND), U9.10 (DEMP), U9.11 (FLT), U9.12 (SCK), U9.16 (FMT), U9.19 (DGND), X1.S (GND); also elsewhere on the board
unnamed: C16.1 (+), C21.1, U9.18 (LDOO)
unnamed: C17.1, U9.4 (CAPM)
unnamed: C17.2, U9.2 (CAPP)
unnamed: R20.2, U9.6 (OUTL)
unnamed: R22.2, U9.7 (OUTR)
unnamed: C19.2, U9.5 (VNEG)
unnamed: C10.2, J1.3, R22.1, X1.R (COLD_R)
unnamed: C9.2, J1.1, R20.1, X1.T (HOT_L)

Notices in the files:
HexAgon.kicad_pcb:
(c) 2025 - S0urceror
